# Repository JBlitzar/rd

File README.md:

# rd

microSD card reader. it exposes microSD cards as a block device that you can read and write to!

Features:
 - dead-simple schematic thanks to the GL823K chip
 - green status LED for activity
 - 4mm keychain hole
 - supports USB 2.0 HS and microSD HS. This means up to 25 MB/s ! 

I made this project because I needed a project scoped to be able to speedrun in 36 hours wall-clock and very little actual working time. It grants me utility-- this way I can read and write to microSD cards super easily in a small form factor, using a dongle I created!! I think microSD cards are uniquely very versatile. There are ones with industrially-rated durability. There are ones that go up to 2TB. There are ones that are so dirt-cheap they cost only a little bit more than the raw NAND inside them. Also, this project unlocks a new ASIC for me that I haven't used before.  

|       |  |
| ----------- | ----------- |
|       |  |

## Schematic

## PCB

## Production outputs like gerbers

Find them in [PCB/rd/production](PCB/rd/production)!

## BOM

Order by uploading the fabrication outputs (linked above) to jlcpcb!

|Item         |Cost |Notes                                                                   |
|-------------|-----|------------------------------------------------------------------------|
|5x PCB (MOQ) |2.0  |order off of JLCONE desktop to save two dollars instead of it costing $4|
|2x PCBA (MOQ)|24.15|                                                                        |
|Shipping     |3.3  |Shipping special offer, otherwise costs 7                               |
|Total        |29.45|                                                                        |

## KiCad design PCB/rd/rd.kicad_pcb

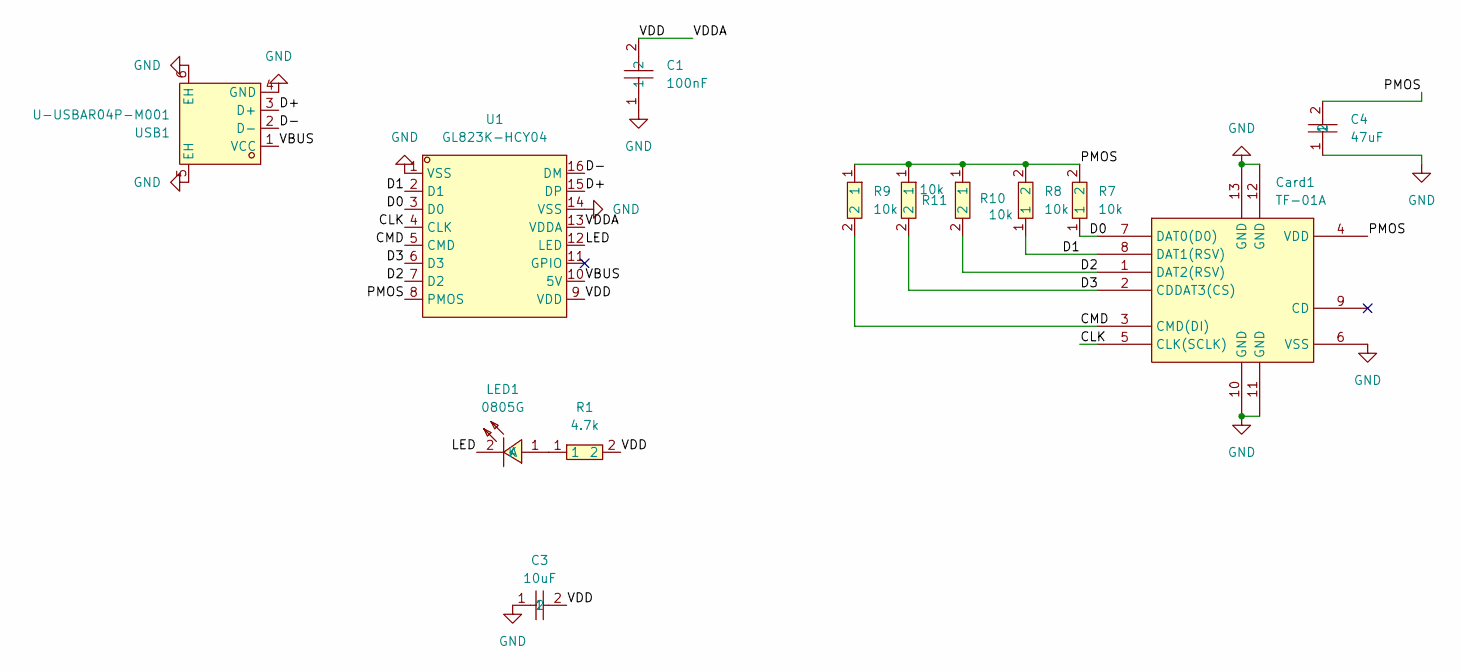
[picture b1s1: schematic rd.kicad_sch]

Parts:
C1: 100nF; C0402; MPN CL05B104KO5NNNC; LCSC Part C1525
C3: 10uF; C0402; MPN CL05A106MQ5NUNC; LCSC Part C15525
C4: 47uF; C0805; MPN CL21A476MQYNNNE; LCSC Part C16780
Card1: TF-01A; TF-SMD_TF-01A; MPN TF-01A; LCSC Part C91145
LED1: 0805G; LED0805-R-RD; MPN KT-0805G; LCSC Part C2297
R1: 4.7k; R0402; MPN 0402WGF4701TCE; LCSC Part C25900
R7, R8, R9, R10, R11: 10k; R0402; MPN 0402WGF1002TCE; LCSC Part C25744
U1: GL823K-HCY04; SSOP-16_L4.9-W3.9-P0.64-LS6.0-BL; MPN GL823K-HCY04; LCSC Part C284879
USB1: U-USBAR04P-M001; USB-SMD_KH-USB-AM-4P-CB; MPN U-USBAR04P-M003; LCSC Part C386752

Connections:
/CLK: Card1.5 (CLK(SCLK)), U1.4 (CLK)
/CMD: Card1.3 (CMD(DI)), R9.2, U1.5 (CMD)
/D0: Card1.7 (DAT0(D0)), R7.1, U1.3 (D0)
/D1: Card1.8 (DAT1(RSV)), R8.1, U1.2 (D1)
/D2: Card1.1 (DAT2(RSV)), R10.2, U1.7 (D2)
/D3: Card1.2 (CDDAT3(CS)), R11.2, U1.6 (D3)
/D+: U1.15 (DP), USB1.3 (D+)
/D-: U1.16 (DM), USB1.2 (D-)
/LED: LED1.2 (K), U1.12 (LED)
/PMOS: C4.2, Card1.4 (VDD), R7.2, R8.2, R9.1, R10.1, R11.1, U1.8 (PMOS)
/VBUS: U1.10 (5V), USB1.1 (VCC)
/VDD: C1.2, C3.2, R1.2, U1.9 (VDD), U1.13 (VDDA)
GND: C1.1, C3.1, C4.1, Card1.6 (VSS), Card1.10 (GND), Card1.11 (GND), Card1.12 (GND), Card1.13 (GND), U1.1 (VSS), U1.14 (VSS), USB1.4 (GND), USB1.5 (EH), USB1.6 (EH)
unnamed: LED1.1 (A), R1.1

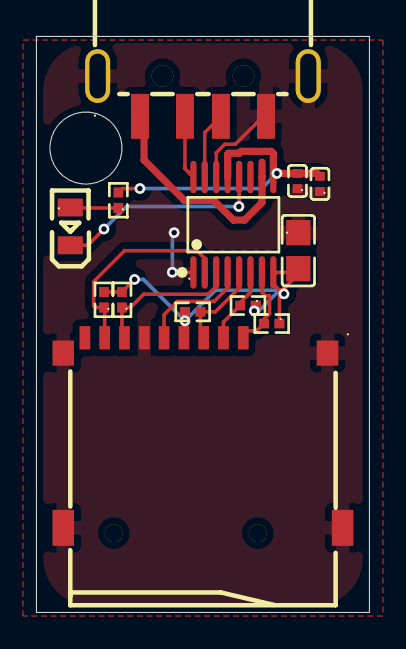
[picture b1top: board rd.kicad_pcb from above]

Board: 2 copper layers, 18.5 x 32.0 mm, 13 parts (0 on the bottom side), 14 nets.
